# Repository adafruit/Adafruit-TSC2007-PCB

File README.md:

## Adafruit TSC2007 I2C Resistive Touch Screen Controller PCB

<a href="http://www.adafruit.com/products/5423"><br/>
Click here to purchase one from the Adafruit shop</a>

PCB files for the Adafruit TSC2007 I2C Resistive Touch Screen Controller. 

Format is EagleCAD schematic and board layout
* https://www.adafruit.com/product/5423

### Description

Getting touchy performance with your screen's touch screen? Resistive touch screens are incredibly popular as overlays to TFT and LCD displays. Only problem is they require a bunch of analog pins and you have to keep polling them since the overlays themselves are basically just big potentiometers. If your microcontroller doesn't have analog inputs, or maybe you want just a way more elegant controller, the TSC2007 is a nice way to solve that problem.

### License

Adafruit invests time and resources providing this open source design, please support Adafruit and open-source hardware by purchasing products from [Adafruit](https://www.adafruit.com)!

Designed by Limor Fried/Ladyada for Adafruit Industries.

Creative Commons Attribution/Share-Alike, all text above must be included in any redistribution. 
See license.txt for additional details.

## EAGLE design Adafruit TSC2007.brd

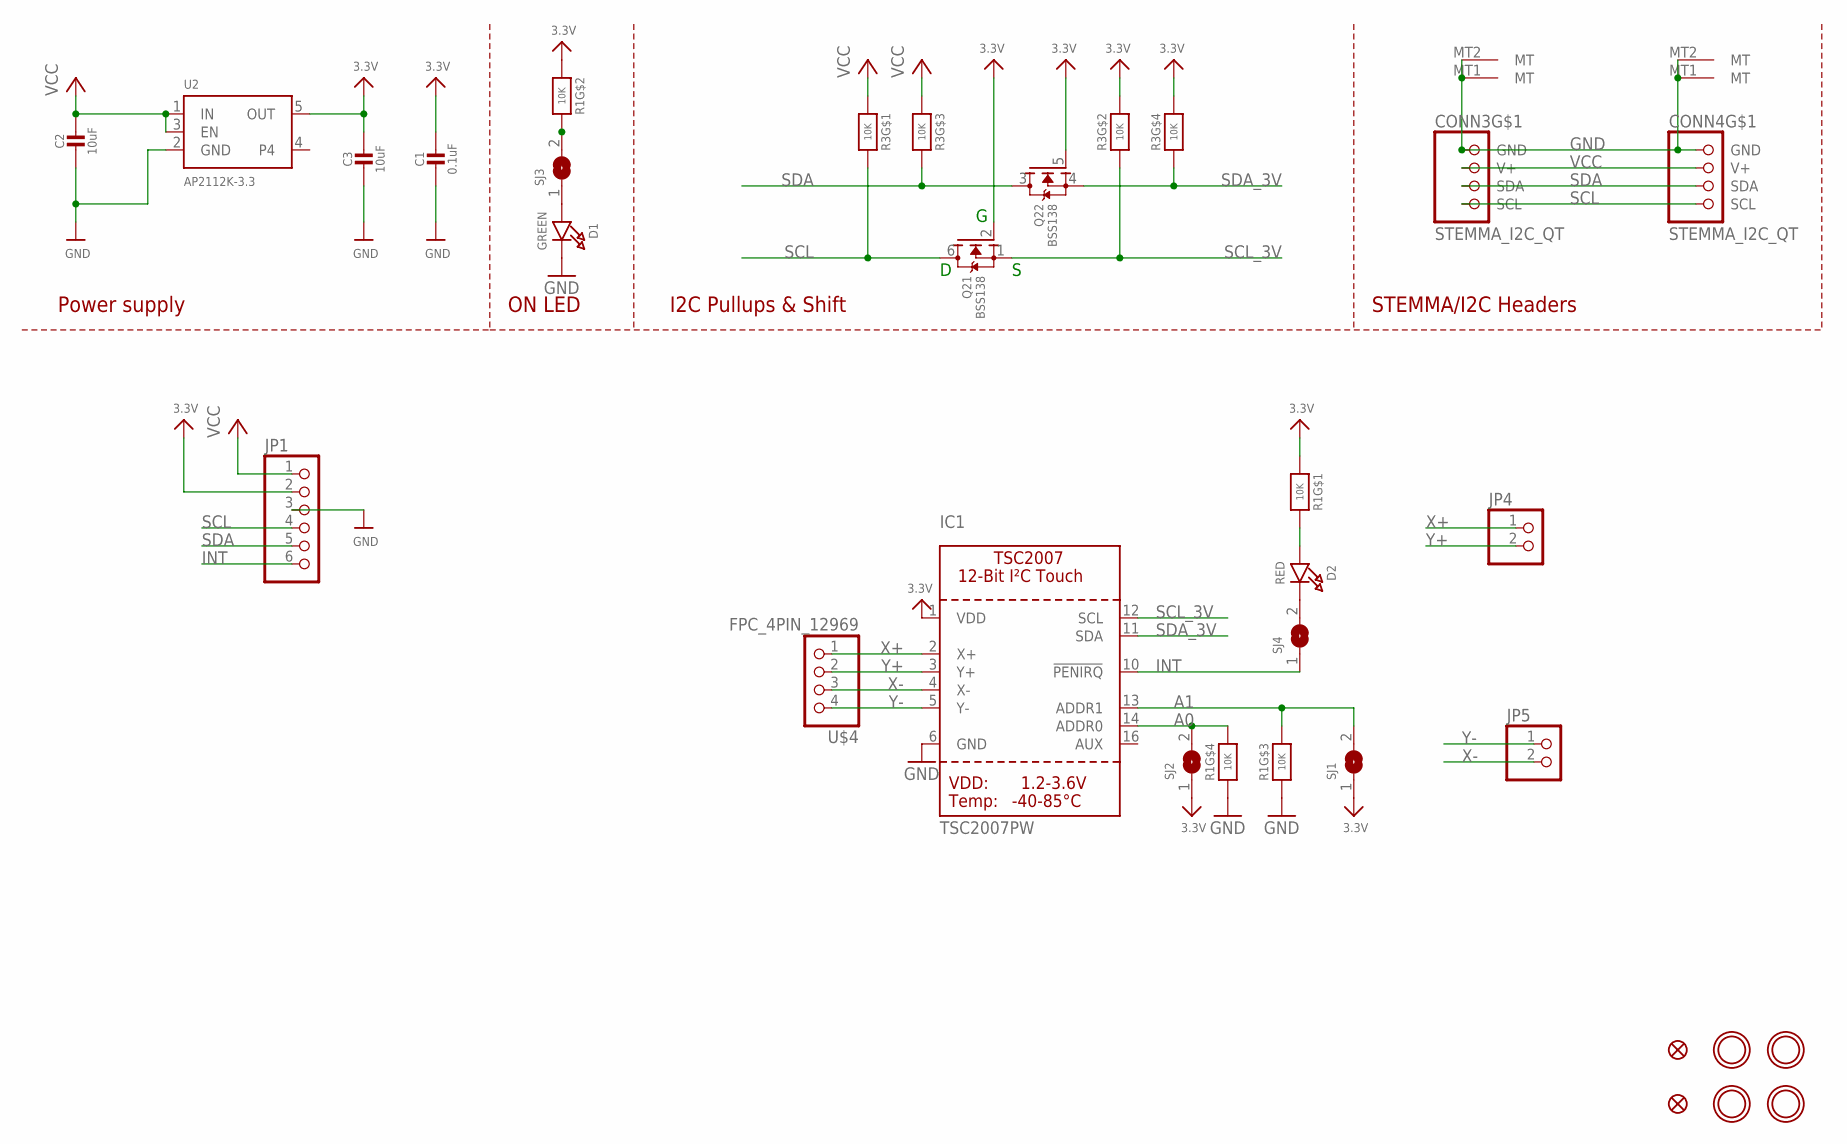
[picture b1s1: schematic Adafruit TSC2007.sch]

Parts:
C1: 0.1uF; 0603-NO
C2, C3: 10uF; 0805-NO
CONN3, CONN4: STEMMA_I2C_QT; JST_SH4
D1: GREEN; CHIPLED_0603_NOOUTLINE
D2: RED; CHIPLED_0603_NOOUTLINE
FID3, FID4: FIDUCIAL_1MM
IC1: TSC2007PW; TSSOP16
JP1: HEADER-1X670MIL; 1X06_ROUND_70
JP4, JP5: HEADER-1X2ROUND; 1X02_ROUND
Q2: BSS138; SOT363
R1, R3: 10K; RESPACK_4X0603
SJ1, SJ2: SOLDERJUMPER; SOLDERJUMPER_ARROW_NOPASTE
SJ3, SJ4: SOLDERJUMPERCLOSED; SOLDERJUMPER_CLOSEDWIRE
U2: AP2112K-3.3; SOT23-5
U$1, U$17, U$19, U$21: MOUNTINGHOLE2.5; MOUNTINGHOLE_2.5_PLATED
U$4: FPC_4PIN_12969; FPC_CONN_1MM_DUAL_4P

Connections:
3.3V: C1.1, C3.1, IC1.1 (VDD), JP1.2, Q2.2 (G), Q2.5 (G), R1.1, R1.2 (1), R3.2 (1), R3.4 (1), SJ1.1, SJ2.1, U2.5 (OUT)
A0: IC1.14 (ADDR0), R1.5 (2), SJ2.2
A1: IC1.13 (ADDR1), R1.6 (2), SJ1.2
GND: C1.2, C2.2, C3.2, CONN3.1 (GND), CONN3.MT1 (MT), CONN3.MT2 (MT), CONN4.1 (GND), CONN4.MT1 (MT), CONN4.MT2 (MT), D1.C, IC1.6 (GND), JP1.3, R1.3 (1), R1.4 (1), U2.2 (GND)
INT: IC1.10 (!PENIRQ), JP1.6, SJ4.1
unnamed: R1.7 (2), SJ3.2
unnamed: D1.A, SJ3.1
unnamed: D2.A, R1.8 (2)
unnamed: D2.C, SJ4.2
SCL: CONN3.4 (SCL), CONN4.4 (SCL), JP1.4, Q2.6 (D), R3.8 (2)
SCL_3V: IC1.12 (SCL), Q2.1 (S), R3.7 (2)
SDA: CONN3.3 (SDA), CONN4.3 (SDA), JP1.5, Q2.3 (D), R3.6 (2)
SDA_3V: IC1.11 (SDA), Q2.4 (S), R3.5 (2)
VCC: C2.1, CONN3.2 (V+), CONN4.2 (V+), JP1.1, R3.1, R3.3 (1), U2.1 (IN), U2.3 (EN)
X+: IC1.2 (X+), JP4.1, U$4.1 (4)
X-: IC1.4 (X-), JP5.2, U$4.3 (2)
Y+: IC1.3 (Y+), JP4.2, U$4.2 (3)
Y-: IC1.5 (Y-), JP5.1, U$4.4 (1)

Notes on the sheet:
I2C Pullups & Shift
STEMMA/I2C Headers
ON LED
Power supply

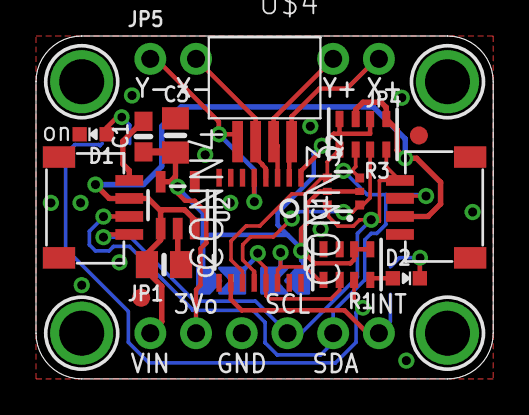
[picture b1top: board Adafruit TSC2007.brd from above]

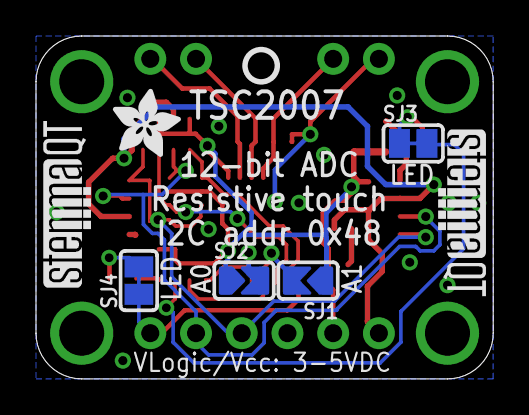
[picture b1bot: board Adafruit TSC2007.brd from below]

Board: 2 copper layers, 25.4 x 19.1 mm, 30 parts (8 on the bottom side), 18 nets.

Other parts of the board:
U$12: ADAFRUIT_3.5MM
U$25: PCBFEAT-REV-040
U$30, U$31: STEMMAQT

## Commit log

2022-04-01 adding cookiecutter output

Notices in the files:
parts and their libraries:
microbuilder: This work is placed in the public domain, and may be freely used for commercial and non-commercial work with the following conditions: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
